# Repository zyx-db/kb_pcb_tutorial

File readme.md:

# hey! im db and im learning to make a keyboard.

my personal goal is to design a pcb for a split keyboard by the end of august 2024. so right now im starting off my learning process by following a [tutorial on how to make a 2x2 keypad](https://wiki.ai03.com/books/pcb-design) (gotta start small)

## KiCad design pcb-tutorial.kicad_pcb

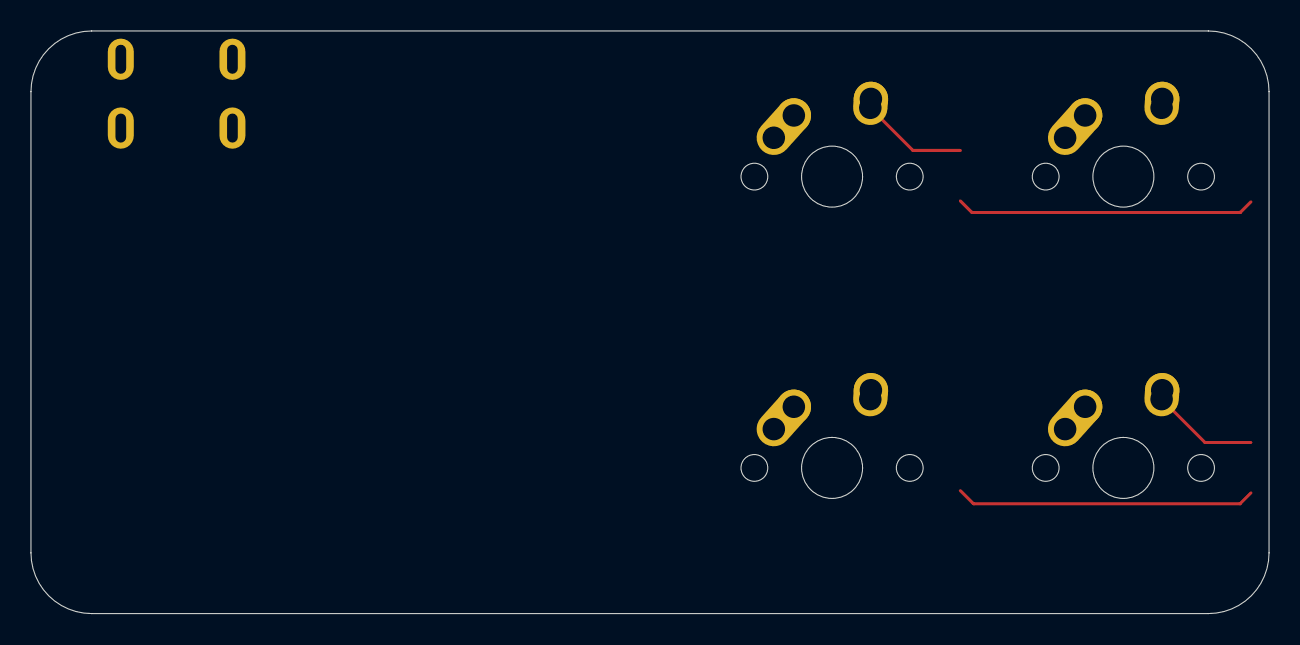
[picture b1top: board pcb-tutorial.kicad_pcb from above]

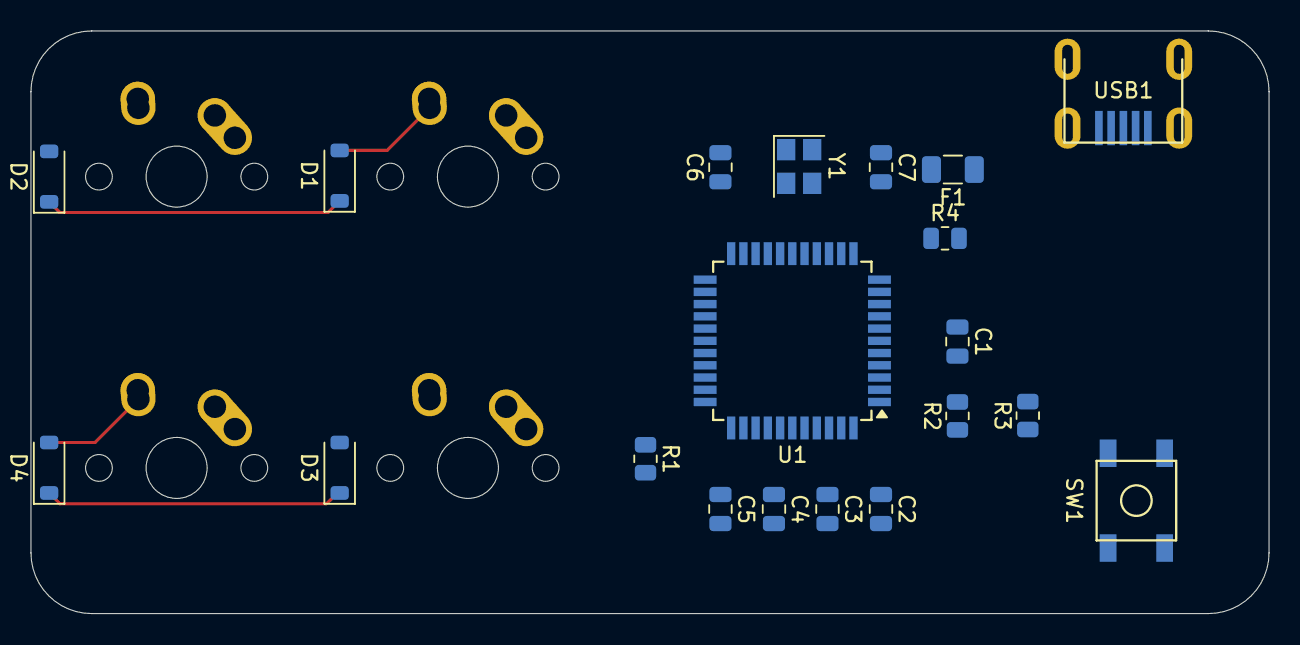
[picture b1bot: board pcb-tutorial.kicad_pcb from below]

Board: 2 copper layers, 81.0 x 38.1 mm, 24 parts (20 on the bottom side), 20 nets.

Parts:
C1: 1uF; C_0805_2012Metric
C2, C3, C4: 0.1uf; C_0805_2012Metric
C5: 10uf; C_0805_2012Metric
C6, C7: 22pF; C_0805_2012Metric
D1, D2, D3, D4: D_Small; D_SOD-123
F1: Polyfuse_Small; Fuse_1206_3216Metric
MX1, MX2, MX3, MX4: MX-NoLED; MX-1U-NoLED
R1: 10K; R_0805_2012Metric
R2, R3: 22; R_0805_2012Metric
R4: 10k; R_0805_2012Metric
SW1: SW_Push; SKQG-1155865
U1: ATmega32U4-A; TQFP-44_10x10mm_P0.8mm
USB1: Molex-0548190589
Y1: Crystal_GND24_Small; Crystal_SMD_3225-4Pin_3.2x2.5mm

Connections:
+5V: C2.1, C3.1, C4.1, C5.1, F1.2, R4.1, U1.2 (UVCC), U1.7 (VBUS), U1.14 (VCC), U1.24 (AVCC), U1.34 (VCC), U1.44 (AVCC)
/col 0: MX1.1 (COL), MX3.1 (COL)
/col 1: MX2.1 (COL), MX4.1 (COL)
/d+: R2.2, USB1.3 (D+)
/d-: R3.1, USB1.4 (D-)
/row 0: D1.1 (K), D2.1 (K)
/row 1: D3.1 (K), D4.1 (K)
GND: C1.2, C2.2, C3.2, C4.2, C5.2, C6.1, C7.1, R1.2, SW1.1, U1.5 (UGND), U1.15 (GND), U1.23 (GND), U1.35 (GND), U1.43 (GND), USB1.1 (GND), Y1.2, Y1.4
unnamed: D1.2 (A), MX1.2 (ROW)
unnamed: D2.2 (A), MX2.2 (ROW)
unnamed: D3.2 (A), MX3.2 (ROW)
unnamed: D4.2 (A), MX4.2 (ROW)
unnamed: R2.1, U1.4 (D+)
unnamed: R3.2, U1.3 (D-)
unnamed: C1.1, U1.6 (UCAP)
unnamed: C6.2, U1.17 (XTAL1), Y1.1
unnamed: C7.2, U1.16 (XTAL2), Y1.3
unnamed: R1.1, U1.33 (~HWB/PE2)
unnamed: R4.2, SW1.2, U1.13 (~RESET)
VCC: F1.1, USB1.5 (VBUS)

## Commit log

2024-07-20 made project, added the mcu
2024-07-20 added the needed component libraries
2024-07-20 readme commit
2024-07-20 added libs to the project
2024-07-20 created mcu schematic
2024-07-27 full schematic
2024-07-27 almost done with pcb, need to route
